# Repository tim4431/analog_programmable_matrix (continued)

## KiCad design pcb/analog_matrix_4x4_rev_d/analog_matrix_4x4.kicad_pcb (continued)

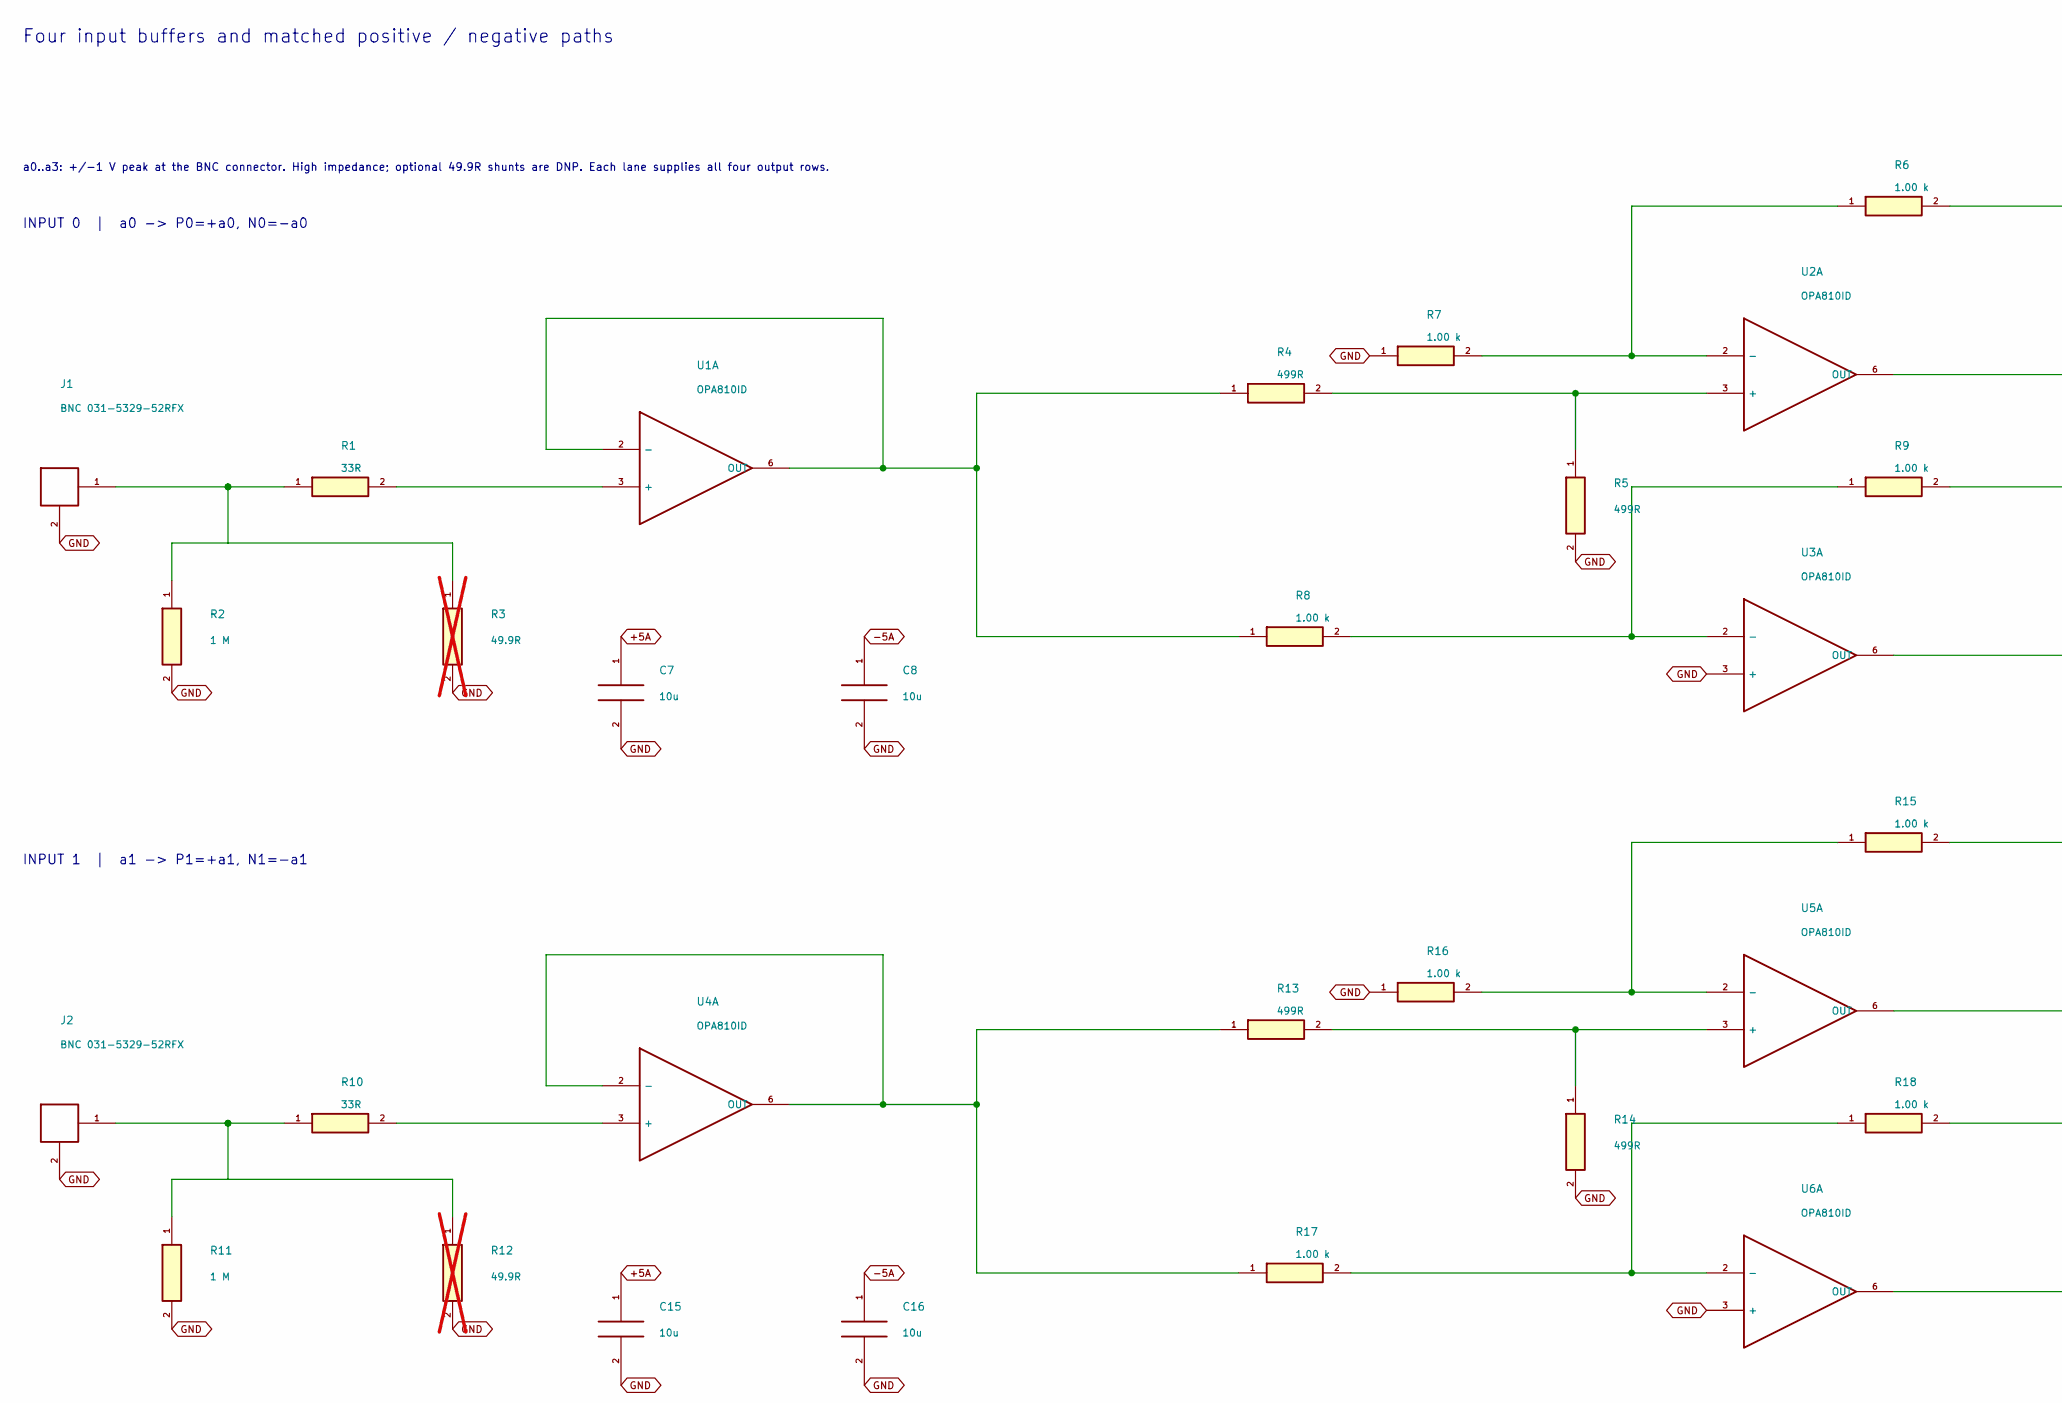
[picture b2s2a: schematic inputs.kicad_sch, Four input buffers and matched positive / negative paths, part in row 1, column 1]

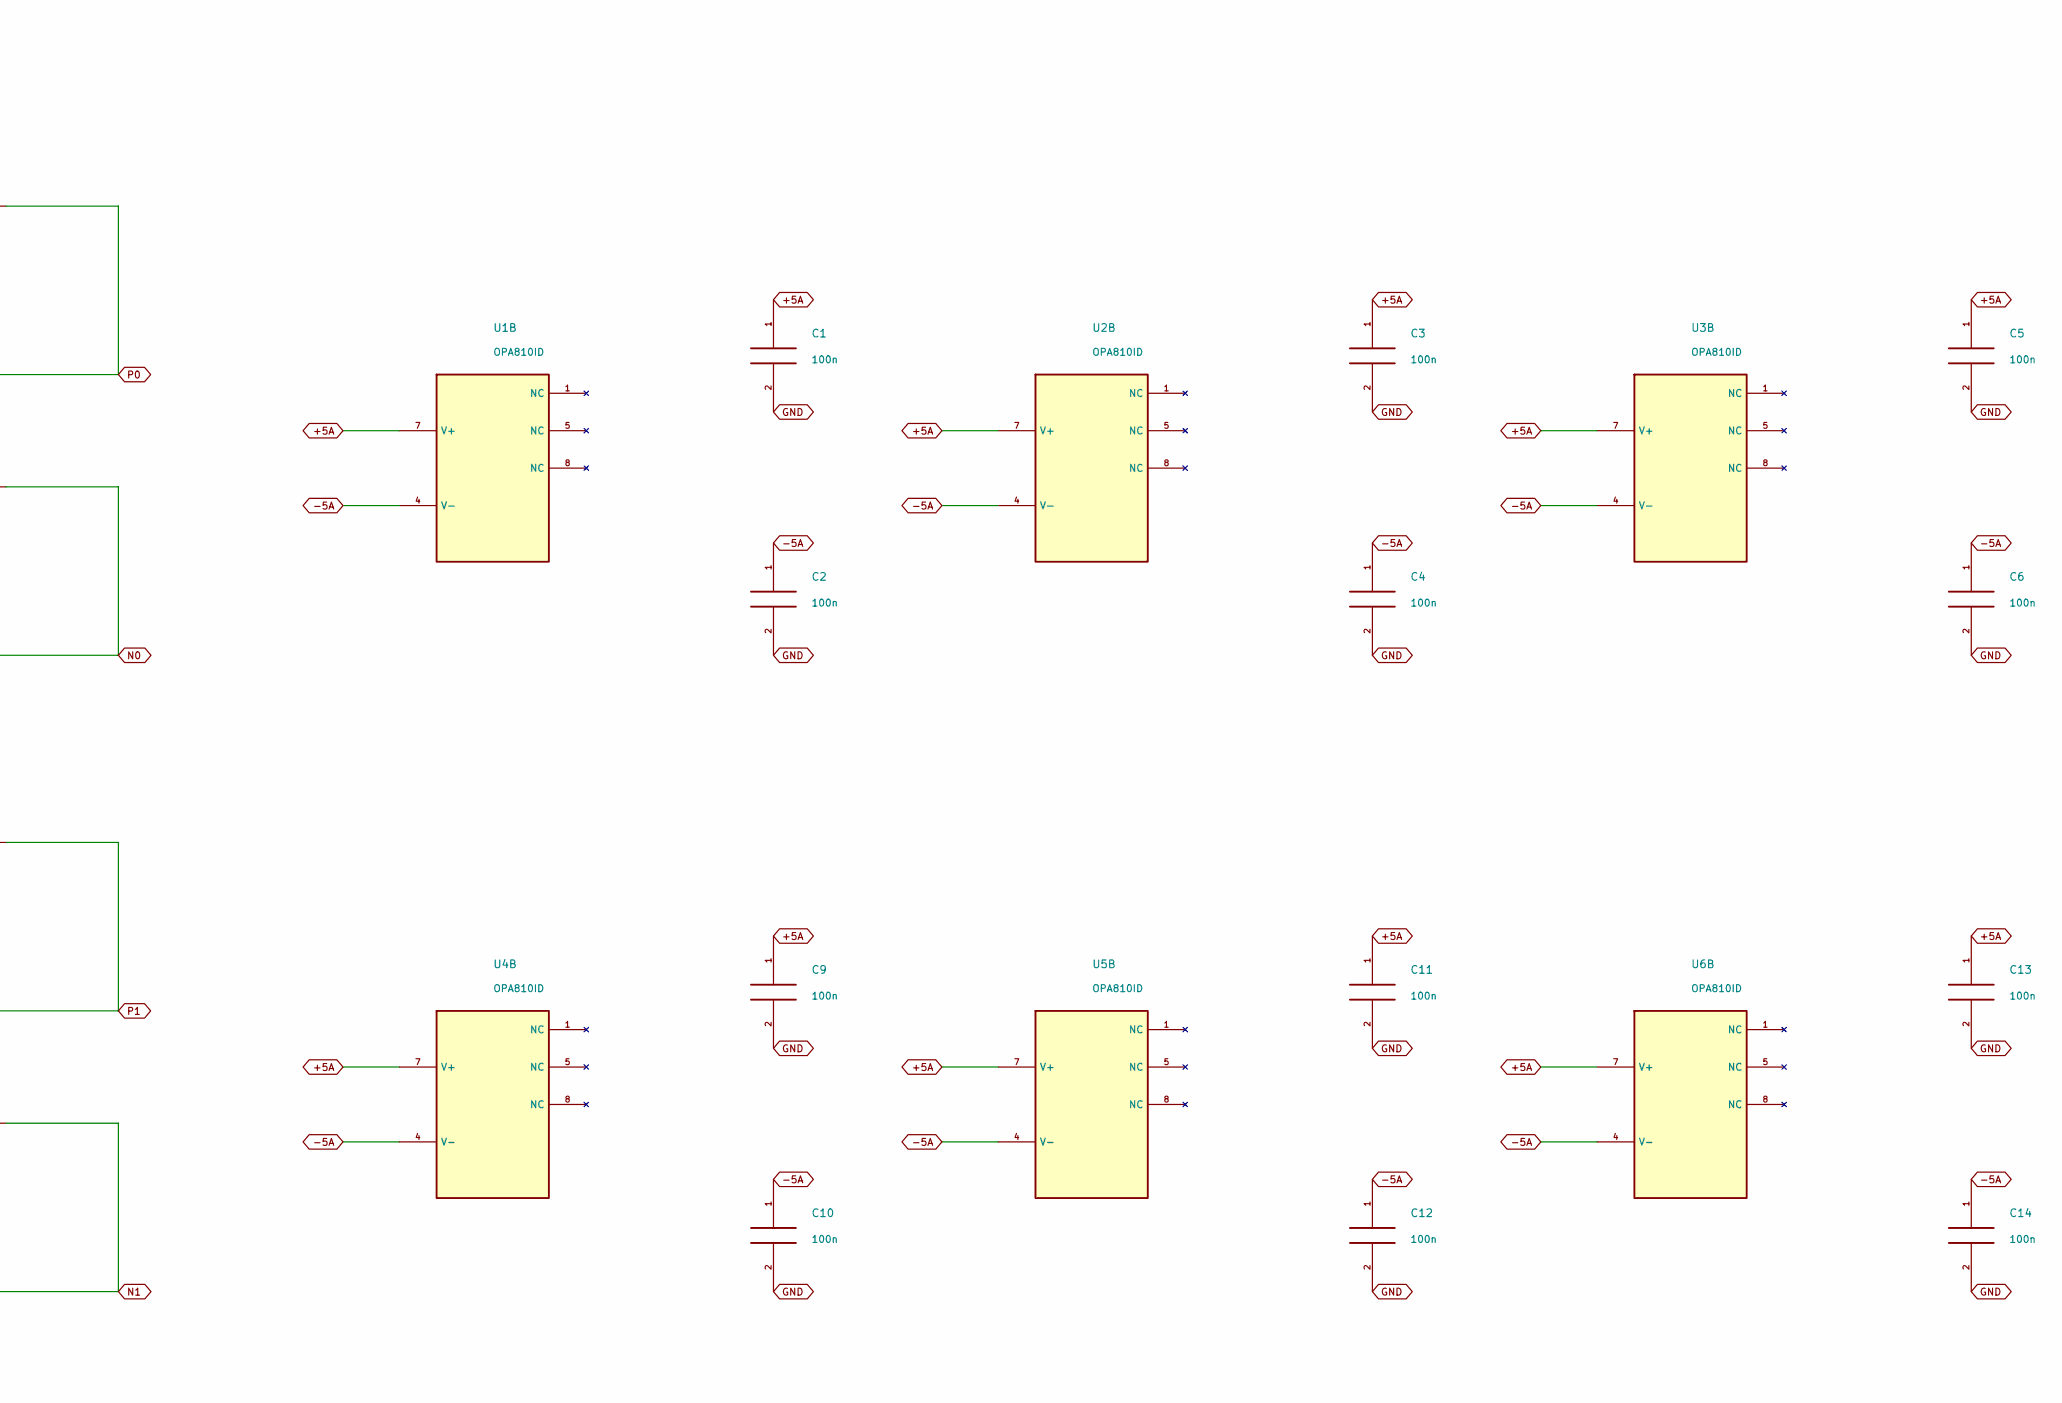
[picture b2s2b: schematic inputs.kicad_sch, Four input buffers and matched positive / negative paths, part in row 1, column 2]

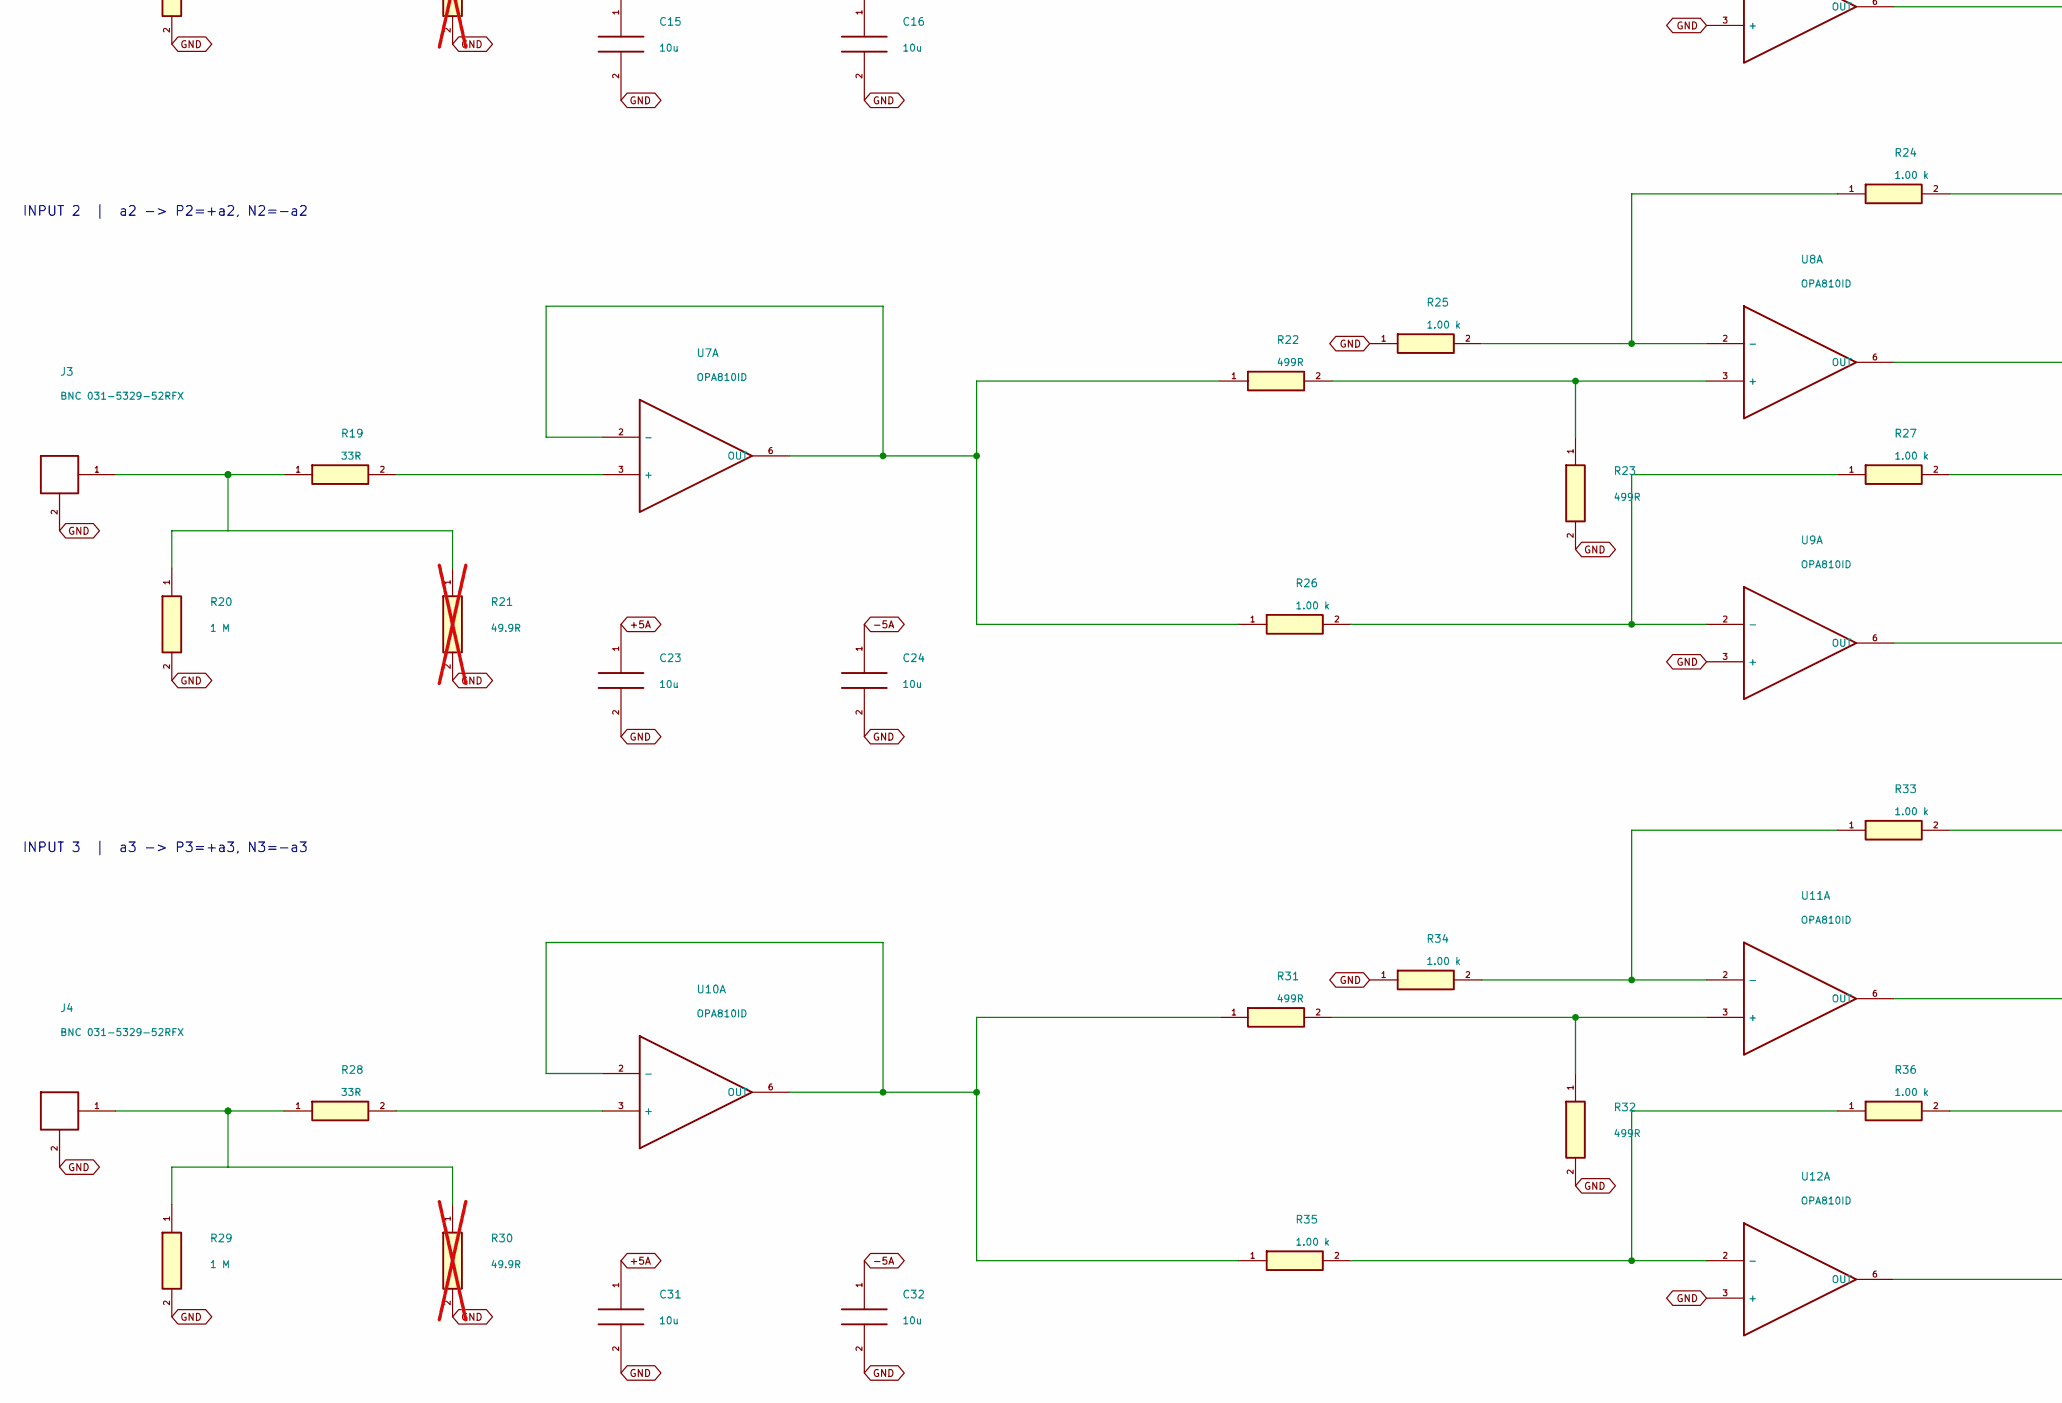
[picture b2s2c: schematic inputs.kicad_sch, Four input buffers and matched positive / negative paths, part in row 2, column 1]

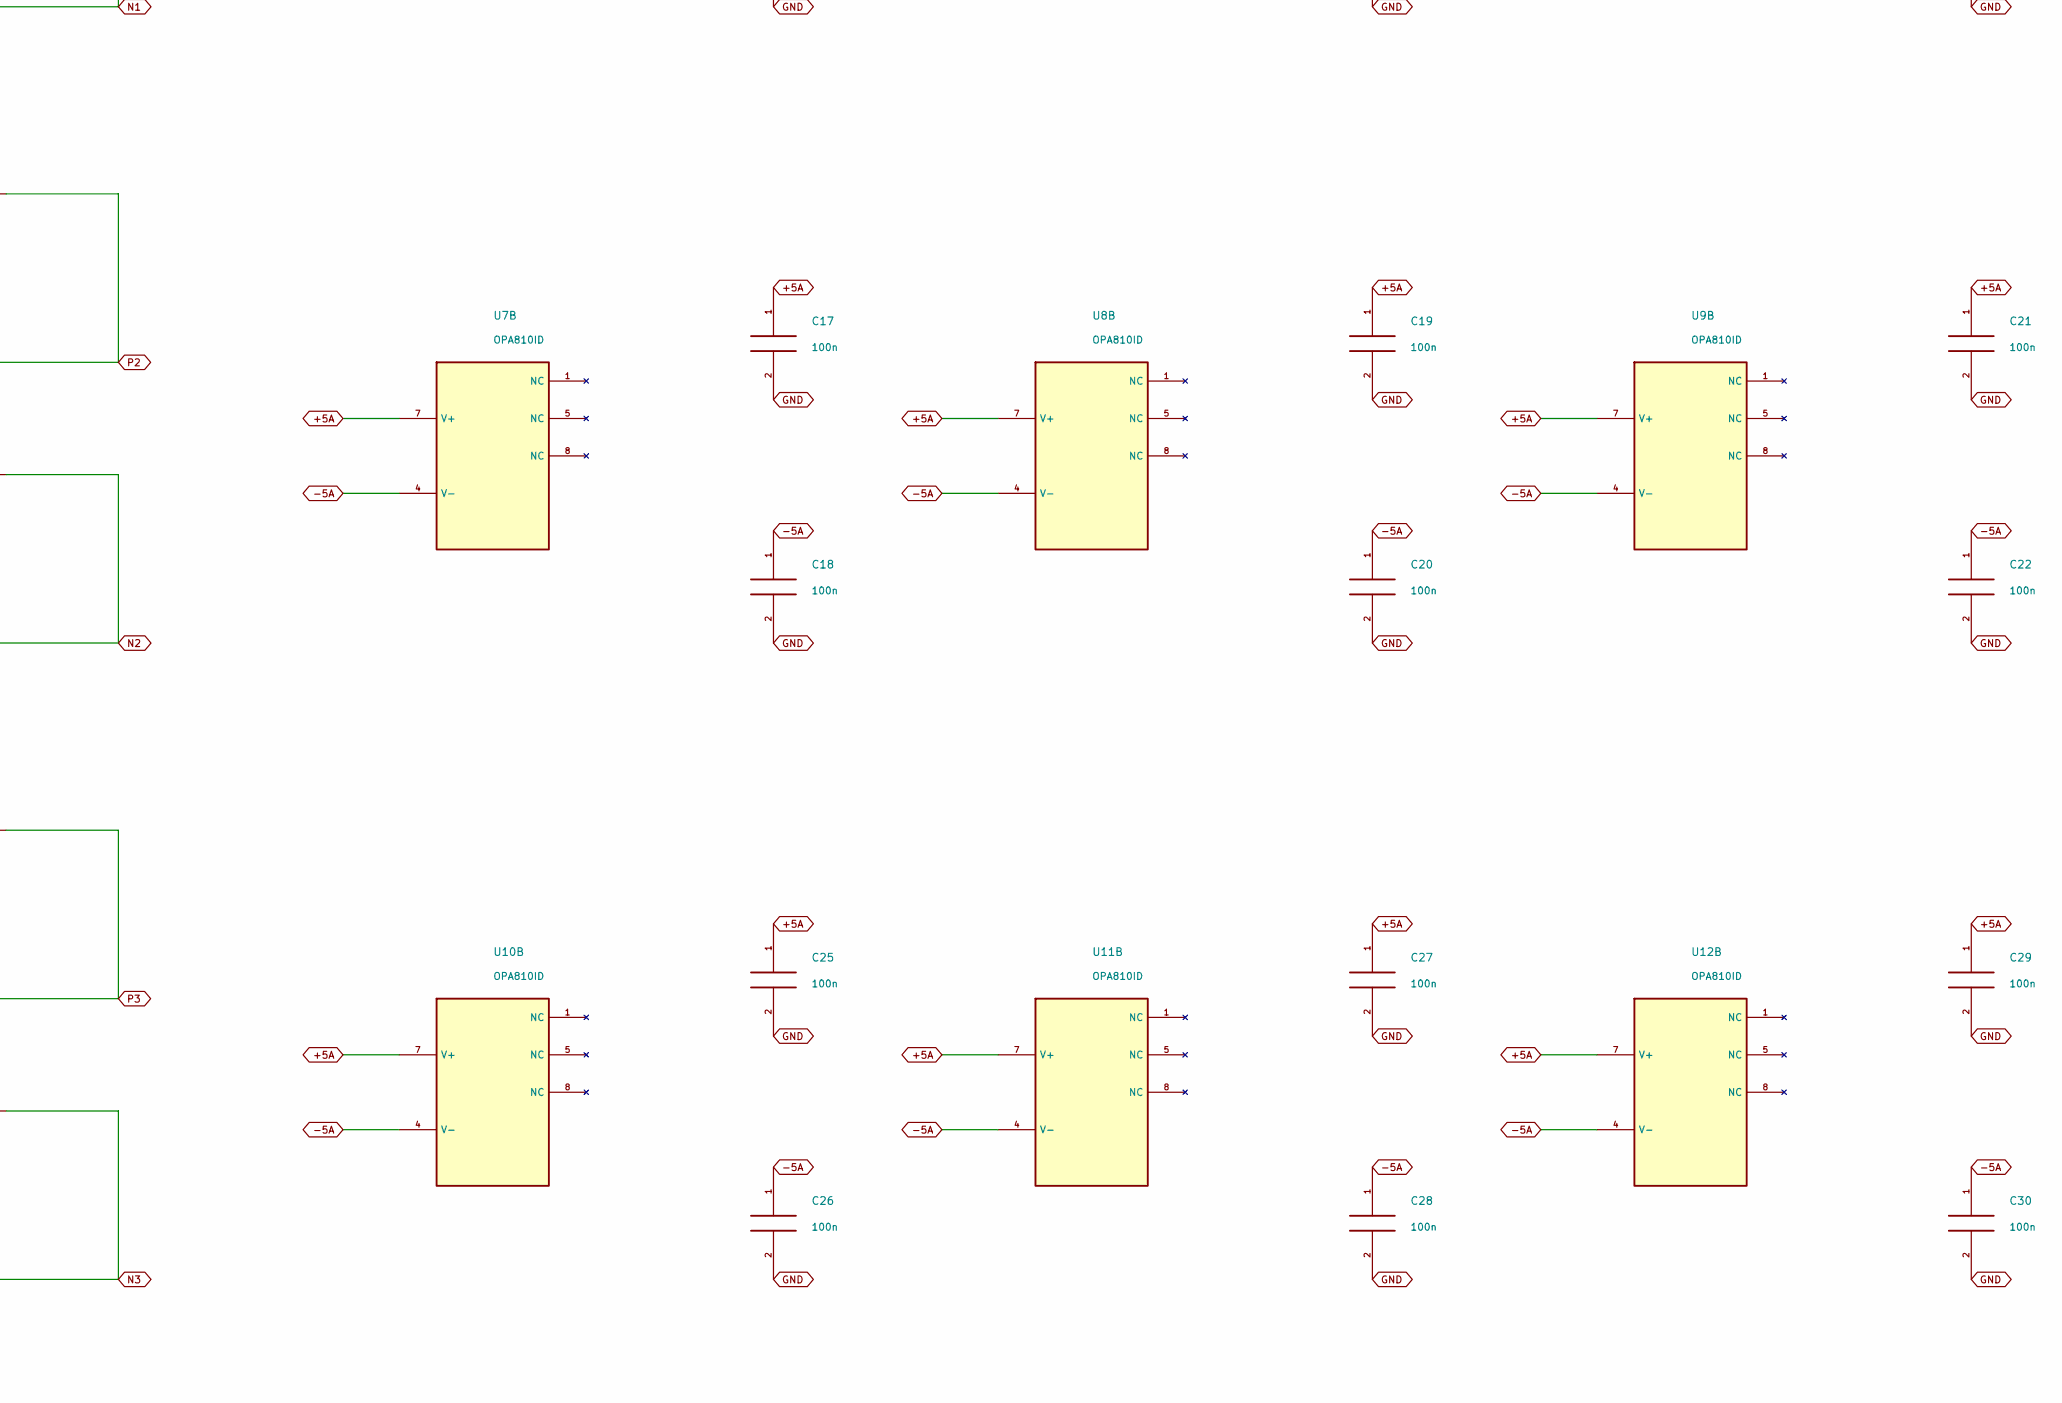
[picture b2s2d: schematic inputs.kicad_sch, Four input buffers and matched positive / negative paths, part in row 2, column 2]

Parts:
C1, C2, C3, C4, C5, C6, C9, C10, C11, C12, C13, C14, C17, C18, C19, C20, C21, C22, C25, C26, C27, C28, C29, C30: 100n; C_0603_1608Metric; Rating 25V X7R minimum; effective C after bias
C7, C8, C15, C16, C23, C24, C31, C32: 10u; C_0805_2012Metric; Rating 25V X7R minimum; effective C after bias
J1, J2, J3, J4: BNC 031-5329-52RFX; BNC_Amphenol_031-5329-52RFX_Vertical
R1, R10, R19, R28: 33R; R_0603_1608Metric; Rating 0.1%, <=25ppm/C; 0.1W minimum
R2, R11, R20, R29: 1 M; R_0603_1608Metric; Rating 0.1%, <=25ppm/C; 0.1W minimum
R3, R12, R21, R30: 49.9R; R_0603_1608Metric; Rating 0.1%, <=25ppm/C; 0.1W minimum; not fitted
R4, R5, R13, R14, R22, R23, R31, R32: 499R; R_0603_1608Metric; Rating 0.1%, <=25ppm/C; 0.1W minimum
R6, R7, R8, R9, R15, R16, R17, R18, R24, R25, R26, R27, R33, R34, R35, R36: 1.00 k; R_0603_1608Metric; Rating 0.1%, <=25ppm/C; 0.1W minimum
U1, U2, U3, U4, U5, U6, U7, U8, U9, U10, U11, U12: OPA810ID; SOIC-8_3.9x4.9mm_P1.27mm

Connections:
+5A: C1.1, C3.1, C5.1, C7.1, C9.1, C11.1, C13.1, C15.1, C17.1, C19.1, C21.1, C23.1, C25.1, C27.1, C29.1, C31.1, U1.7 (V+), U2.7 (V+), U3.7 (V+), U4.7 (V+), U5.7 (V+), U6.7 (V+), U7.7 (V+), U8.7 (V+), U9.7 (V+), U10.7 (V+), U11.7 (V+), U12.7 (V+); also elsewhere on the board
-5A: C2.1, C4.1, C6.1, C8.1, C10.1, C12.1, C14.1, C16.1, C18.1, C20.1, C22.1, C24.1, C26.1, C28.1, C30.1, C32.1, U1.4 (V-), U2.4 (V-), U3.4 (V-), U4.4 (V-), U5.4 (V-), U6.4 (V-), U7.4 (V-), U8.4 (V-), U9.4 (V-), U10.4 (V-), U11.4 (V-), U12.4 (V-); also elsewhere on the board
GND: C1.2, C2.2, C3.2, C4.2, C5.2, C6.2, C7.2, C8.2, C9.2, C10.2, C11.2, C12.2, C13.2, C14.2, C15.2, C16.2, C17.2, C18.2, C19.2, C20.2, C21.2, C22.2, C23.2, C24.2, C25.2, C26.2, C27.2, C28.2, C29.2, C30.2, C31.2, C32.2, J1.2, J2.2, J3.2, J4.2, R2.2, R3.2, R5.2, R7.1, R11.2, R12.2, R14.2, R16.1, R20.2, R21.2, R23.2, R25.1, R29.2, R30.2, R32.2, R34.1, U3.3 (+), U6.3 (+), U9.3 (+), U12.3 (+); also elsewhere on the board
N0: R9.2, U3.6 (OUT); also elsewhere on the board
N1: R18.2, U6.6 (OUT); also elsewhere on the board
N2: R27.2, U9.6 (OUT); also elsewhere on the board
N3: R36.2, U12.6 (OUT); also elsewhere on the board
unnamed: J1.1, R1.1, R2.1, R3.1
unnamed: J2.1, R10.1, R11.1, R12.1
unnamed: J3.1, R19.1, R20.1, R21.1
unnamed: J4.1, R28.1, R29.1, R30.1
unnamed: R1.2, U1.3 (+)
unnamed: R4.1, R8.1, U1.2 (-), U1.6 (OUT)
unnamed: R4.2, R5.1, U2.3 (+)
unnamed: R6.1, R7.2, U2.2 (-)
unnamed: R8.2, R9.1, U3.2 (-)
unnamed: R10.2, U4.3 (+)
unnamed: R13.1, R17.1, U4.2 (-), U4.6 (OUT)
unnamed: R13.2, R14.1, U5.3 (+)
unnamed: R15.1, R16.2, U5.2 (-)
unnamed: R17.2, R18.1, U6.2 (-)
unnamed: R19.2, U7.3 (+)
unnamed: R22.1, R26.1, U7.2 (-), U7.6 (OUT)
unnamed: R22.2, R23.1, U8.3 (+)
unnamed: R24.1, R25.2, U8.2 (-)
unnamed: R26.2, R27.1, U9.2 (-)
unnamed: R28.2, U10.3 (+)
unnamed: R31.1, R35.1, U10.2 (-), U10.6 (OUT)
unnamed: R31.2, R32.1, U11.3 (+)
unnamed: R33.1, R34.2, U11.2 (-)
unnamed: R35.2, R36.1, U12.2 (-)
P0: R6.2, U2.6 (OUT); also elsewhere on the board
P1: R15.2, U5.6 (OUT); also elsewhere on the board
P2: R24.2, U8.6 (OUT); also elsewhere on the board
P3: R33.2, U11.6 (OUT); also elsewhere on the board

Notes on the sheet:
Four input buffers and matched positive / negative paths
a0..a3: +/-1 V peak at the BNC connector. High impedance; optional 49.9R shunts are DNP. Each lane supplies all four output rows.
INPUT 0 | a0 -> P0=+a0, N0=-a0
INPUT 1 | a1 -> P1=+a1, N1=-a1
INPUT 2 | a2 -> P2=+a2, N2=-a2
INPUT 3 | a3 -> P3=+a3, N3=-a3
